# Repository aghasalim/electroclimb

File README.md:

<h1 align="center">ElectroClimb</h1>

<p align="center"><strong>An open-source legged robot that climbs concrete, glass and wood on electroadhesive feet,<br>controlled by reinforcement learning, and inspects structures as it goes.</strong></p>

<p align="center">
  <a href="docs/HOW_IT_WORKS.md">How it works</a> ·
  <a href="#the-model">The model</a> ·
  <a href="#ai-in-electroclimb">AI</a> ·
  <a href="docs/WALLSCAN.md">WallScan</a> ·
  <a href="hardware/foot/BUILD.md">Build a foot</a> ·
  <a href="sim/README.md">Simulation</a> ·
  <a href="inspection/README.md">Inspection</a> ·
  <a href="#roadmap">Roadmap</a>
</p>

> **Status:** everything here runs in simulation. **New (25 Nov 2026):** the robot now steers in any direction, goes from a wall onto a ceiling through a corner and trots under a ceiling on two pads, all with pads that only grip when flat. The same check showed the earlier results were too kind (pads gripped on their edges; the 88 % on hard walls becomes 42 %, or 82 % with a faster gait clock) and that the ankle must be much softer (the foot and hip CAD are changed to match, not yet printed): [`sim/README.md`](sim/README.md#flat-pads-steering-the-corner-and-the-ceiling-trot). The simulated robot climbs a vertical wall; the foot hardware (stage 1) is in progress. See [`hardware/foot/`](hardware/foot/) and [`sim/`](sim/).

<p align="center"><em>MuJoCo simulation, vertical wall and a 40 cm concrete pillar, 2× speed: baseline crawl gait with electroadhesive feet, 18 cm in 20 s without falling. Real physics, not an animation.</em></p>

<details>
<summary>Contents</summary>

- [The model](#the-model)
- [Repository](#repository)
- [Why](#why)
- [What makes it new](#what-makes-it-new)
- [How it works](#how-it-works)
- [AI in ElectroClimb](#ai-in-electroclimb)
- [New idea: WallScan, feet that see inside the wall](#new-idea-wallscan-feet-that-see-inside-the-wall)
- [The robot](#the-robot)
- [The learning](#the-learning)
- [Roadmap](#roadmap)
- [Hard problems](#hard-problems)
- [Who it's for](#who-its-for)
- [License](#license)
- [Author](#author)
- [Related work](#related-work)

</details>

## The model

| Part | What's modelled |
|---|---|
| **Motors** | 12 STS3215 servos (45.2 × 24.7 × 35 mm) in their mounting positions: 4 abduction servos in the chassis corners, 4 hip servos bolted to their horns, 4 knee servos built into the shins. Horns, case screws, mounting ears and cable exits included. |
| **Legs** | One outboard thigh plate per leg between the hip horn and the knee horn, a carbon shin tube, a ball ankle and the red high-voltage cable down each shin. |
| **Feet** | Flex-PCB pad with the two interdigitated copper combs, a TPU spider, and the HV driver board (HV module, reed relay, resistors, LED). Pads and LEDs glow while energised. |
| **Brain** | Electronics bay under a clear lid: brain PCB (CPU with heat sink and fan, RAM, flash, 4 CAN transceivers, IMU, GPIO header, leg connectors) and a power board. |
| **Enclosure** | Graphite chassis tub with cooling fins and grab rails, white bay rim, stereo camera nose with an inspection light, tail block with tether ring, antenna, e-stop and charge port, battery strapped under the belly. |

The whole model is generated by [`sim/make_assets.py`](sim/make_assets.py) (70 meshes, 36,000 triangles, 4 textures). It is visual only: the detailed parts have no mass and no contacts, so mass (1.46 kg), inertia and every simulation result are unchanged. It shows the intended layout; it is not a CAD model for manufacturing. The first real CAD is the foot: [`hardware/foot/cad/`](hardware/foot/cad/).

## Repository

| Path | What's there |
|---|---|
| [`hardware/foot/`](hardware/foot/) | Stage 1 foot: design spec, pad footprints (KiCad), BOM, **real CAD (STEP/STL)** and a [build guide](hardware/foot/BUILD.md) |
| [`hardware/`](hardware/README.md) | **Whole-robot hardware design** (not built): system scheme, wiring diagram, [bill of materials](hardware/BOM.md), the [driver board](hardware/foot/driver/) as a rule-checked KiCad PCB with Gerbers, and [body and leg CAD](hardware/robot/cad/) |
| [`tools/gen_electrode.py`](tools/gen_electrode.py) | Parametric electrode pad generator (`--selftest` checks for shorts) |
| [`tools/driver_calc.py`](tools/driver_calc.py) | HV driver component values + design-rule checks |
| [`sim/`](sim/) | MuJoCo model, climbing environment, crawl gait, physics checks, media renderer (stage 2) |
| [`inspection/`](inspection/) | Crack-detection CNN, RAG inspection assistant, LLM mission planner (stage 5) |
| [`sensing/`](sensing/) | WallScan: field solver and network for sensing inside the wall with the pad electrodes (simulation study) |
| [`media/`](media/) | Simulation GIFs and images (rendered by `sim/render_media.py`) |
| [`docs/HOW_IT_WORKS.md`](docs/HOW_IT_WORKS.md) | How it works: leg mechanism, gait, electroadhesion physics, peel moment, balance on three legs, HV driver, RL loop, results |
| [`docs/DESIGN.md`](docs/DESIGN.md), [`docs/LAUNCH_POSTS.md`](docs/LAUNCH_POSTS.md) | Visual language of the banner and images; draft launch posts |
| [`docs/`](docs/) | Sponsorship sheet |

## Why

Every bridge, dam, tower and facade needs regular inspection. Today that means scaffolding, rope access or drones that can't touch the surface. A robot that walks up the wall itself can get close enough to measure a crack, tap the concrete and come back down.

Climbing robots with learned controllers already exist, but they cling to **steel** with magnets. Most of the built world is concrete, glass, brick and wood, where magnets don't work.

**Electroadhesion** works on almost any surface. A thin pad with interdigitated electrodes at 1–3 kV (microamp current) induces charge in the surface and sticks to it, then releases instantly when switched off. The hard part is that adhesion depends on the surface, dust, humidity and how flat the contact is, and one bad step means a fall.

ElectroClimb treats that as a learning problem. Each foot senses its own grip through electrode capacitance, and a reinforcement learning policy decides where to step, how hard to press, when to energise each foot and when to peel it off.

## What makes it new

| | Existing learned climbers | ElectroClimb |
|---|---|---|
| Adhesion | Magnets (steel only) | Electroadhesion (concrete, glass, wood, painted walls) |
| Grip sensing | Assumed or estimated | Measured per foot (electrode capacitance) |
| Control | RL for walking, fixed adhesion | RL controls walking **and** adhesion (voltage, timing, peel) |
| Openness | Closed, research hardware | Fully open hardware, firmware, simulation, policies |
| Cost target | Lab robots | Under €2,000 in parts |

## How it works

<p align="center"><em>One leg stepping: the pad lets go, the foot lifts 2.5 cm, moves 4 cm up and sticks again.</em></p>

```mermaid
mindmap
  root((ElectroClimb))
    Legs
      3 servos per leg, 12 in total
      Thigh 8.1 cm, shin 6.7 cm
      Spring ankles keep pads flat
    Electroadhesion
      Comb electrodes at 1 to 3 kV
      Friction carries the weight
      Split pads survive drop-outs
    Sensing
      Pad capacitance shows contact
      IMU and servo positions
    Control
      Crawl gait, one leg at a time
      Never lift until 3 feet stick
      RL corrects the gait
```

- **Legs:** each leg has hip abduction, hip flexion and knee servos (Feetech STS3215). Inverse kinematics turns planned foot positions into joint angles. On a vertical wall the gait needs at most 0.9 N·m per joint.
- **Gait:** one foot moves at a time (release, lift, swing 4 cm, place until contact, stick), then the body pulls itself up on all four pads. A foot is only released when the other three report contact.
- **Physics:** the pads press the robot against the wall and friction carries the weight: 0.6 × pads × 15 N × grip must beat 14.3 N. With three pads that needs at least 53 % grip. The weight 9 cm from the wall also tries to peel the upper feet off (about 6.4 N), which is why the body crouches low.
- **Electronics:** each pad half has its own high-voltage driver board (XP Power A30P-5, 0–3 kV, microamp-limited), with a 1 GΩ safety bleeder and a reed relay that releases the pad in about 1 ms. The board is designed and rule-checked, not built: [`hardware/foot/driver/`](hardware/foot/driver/).

### How the feet stick

On a floor the robot needs no adhesion: gravity holds it down. On walls and ceilings it uses electroadhesion.

1. **The pad is a flexible circuit board.** Under a thin insulating layer it has two comb-shaped electrodes that interleave like fingers of two hands.
2. **A high voltage goes across the two combs:** 1 to 3 kV, one comb positive and one negative. The current is only microamps, so a pad uses well under a watt.
3. **The surface responds.** The electric field shifts charges inside the wall material under the pad. Opposite charges attract, so the pad is pulled onto the wall.
4. **On a wall, friction carries the weight.** The pull presses the pad against the surface and friction stops it sliding down. Under a ceiling the pull itself carries the weight.
5. **Switching off releases the foot.** A relay discharges the pad in about 1 ms, so the leg can lift and step.

It needs no air-tight seal like suction and no steel like magnets, so it works on glass, wood and painted concrete.

Two limits:

- **The pad must lie flat.** The pull only acts across a gap of micrometres. A pad tilted more than a few degrees does not grip, which is why each foot has a soft ankle ([`sim/README.md`](sim/README.md)).
- **The force is not measured yet.** The simulation assumes 15 N per pad. Rough, dusty or damp surfaces give less, and the first bench test of a real pad will give the true number.

**Standing on three legs.** Every step leaves three pads holding the robot. On a vertical wall that needs 55–58 % grip instead of 41 % on four pads, and lifting an upper leg is the worst case. A force model and MuJoCo agree on these numbers ([`sim/balance.py`](sim/balance.py)).

**Full explanation with diagrams: [docs/HOW_IT_WORKS.md](docs/HOW_IT_WORKS.md).**

### Latest simulation results

Success = no fall and at least 10 cm climbed in 20 s on 40 hard vertical test walls.

| | Success | Falls |
|---|---|---|
| Crawl gait, one-piece pads | 80 % | 15 % |
| Best RL policy, one-piece pads | 82 % | 12 % |
| **Crawl gait, split pads** | **88 %** | **12 %** |
| RL policy, split pads | 88 % | 12 % |
| Crawl gait, split pads, +10 % pad force | **95 %** | **2 %** |

Splitting each pad into two independently driven halves fixes random pad drop-outs. The rest is a margin question: about 10 % more pad force (bigger pads or a lighter robot) takes the plain gait to 95 %. Details in [`sim/README.md`](sim/README.md).

## AI in ElectroClimb

| Part | Method | Result | Code |
|---|---|---|---|
| Climbing control | Residual RL on a crawl gait: PPO, SAC, curriculum, teacher-student distillation (DAgger) | 88 % on 40 hard walls; 95 % with 10 % more pad force | [`sim/`](sim/README.md) |
| Crack detection | CNN on 40,000 concrete photos, tile scan of wall images | 99.25 % on 4,000 unseen photos | [`inspection/crack_model.py`](inspection/crack_model.py) |
| Inspection assistant | RAG: BM25 over the FHWA Bridge Inspector's Reference Manual + Claude with page citations | answers and defect reports cite manual pages | [`inspection/rag.py`](inspection/rag.py) |
| Subsurface sensing (WallScan) | Finite-difference field model + neural inverse on 36 electrode-pair capacitances | 91 % defect identification in simulation; untested on hardware | [`sensing/wallscan.py`](sensing/wallscan.py) |
| Mission planning | LLM (Claude) turns a sentence into a checked waypoint plan the robot climbs in simulation | holds within 0.03 cm at each inspection stop | [`inspection/mission.py`](inspection/mission.py) |
| Talking to the robot | Spoken orders and questions while it climbs: rules offline, Claude for free sentences; answers out loud | inspect, stop, resume, grip check, come down and report in one run | [`inspection/voice.py`](inspection/voice.py) |

Details: [`inspection/README.md`](inspection/README.md) and [`sim/README.md`](sim/README.md).

## New idea: WallScan, feet that see inside the wall

The pads that hold the robot could also scan the wall. With each pad's comb split into 8 separately wired strips, the 36 strip-pair capacitances carry information about what is under the foot. In a first simulation study, a neural network identifies voids, wet zones and rebar correctly in **91 %** of unseen footsteps and locates them within 2.4 mm sideways and 1.1 mm in depth; one capacitance per pad (today's grip sensing) manages 32 %. In a literature search, no published climbing robot was found that uses its adhesion electrodes to image the wall. This is simulation only, not yet measured on hardware. Details, sources and limits: [`docs/WALLSCAN.md`](docs/WALLSCAN.md).

## The robot

- **Body:** quadruped, about 40 cm and under 1.5 kg, with a 3D-printed carbon-fibre-nylon frame.
- **Legs:** 3 actuated joints per leg (12 total), using low-cost smart servos at first and custom quasi-direct-drive actuators in v2.
- **Feet:** flexible-PCB electroadhesive pads (polyimide doubles as the insulator) on compliant TPU backings, with a passive ankle so each pad can lie flat.
- **Foot electronics:** a small high-voltage driver per pad half (two per foot, so one fault only loses half a pad), current-limited, and a capacitance-sensing front end on the same electrodes for grip and contact sensing.
- **Compute:** Seeed XIAO microcontrollers per leg on a CAN bus, and a Raspberry Pi 5 or Jetson Orin Nano running the policy and vision.
- **Sensing:** IMU, joint encoders and currents, per-foot capacitance, front stereo camera.
- **Safety:** tether line during development, fall detection, and a hardware interlock so the high voltage is only on when the foot is in contact.

## The learning

1. **Adhesion model:** measure holding force against voltage, surface, dust, humidity and peel angle on a test rig. Fit a stochastic adhesion model to that data.
2. **Simulation:** model the robot in MuJoCo / Isaac Lab with the learned adhesion model, including random attachment failures, surface patches and dust.
3. **Curriculum RL:** train on thousands of parallel simulated environments while slowly tilting gravity from floor to vertical wall to overhang. Domain randomisation covers adhesion, friction, motor strength, latency and sensor noise.
4. **Teacher-student:** a teacher policy that sees true adhesion trains a student policy that only sees what the real robot senses (capacitance, IMU, joints).
5. **Sim-to-real:** deploy on the robot, tethered, first on a tilting test wall, then vertical, then real structures.
6. **Inspection:** an onboard vision model detects cracks and spalling, and the robot builds a 3D map of the wall with defects marked.

## Roadmap

| Stage | Goal | Done when |
|---|---|---|
| **1. Electroadhesive foot** (months 1–3) | Pad design, high-voltage driver, capacitance sensing, adhesion test rig | Reliable hold on concrete, glass and wood, and grip measured from capacitance |
| **2. Adhesion model + simulation** (months 2–5) | Data-driven adhesion model, robot simulation, first trained climbing policy in sim | A policy climbs a vertical wall in simulation and survives random adhesion failures |
| **3. Robot v1** (months 4–7) | Build the quadruped and electronics, and get it walking on the floor | Walks with an RL policy transferred from simulation |
| **4. Real climbing** (months 6–10) | Tilt-wall curriculum on hardware, then vertical | Climbs 2 m of vertical concrete and glass on a tether, without falling |
| **5. Inspection** (months 9–12) | Crack-detection model, mapping, floor-to-wall transitions | Climbs a real wall and returns a map of defects |
| **6. Release** (month 12) | Build guide, datasets, trained policies, paper | Everything open, and a paper submitted (ICRA / IROS / RA-L) |

## Hard problems

- **Adhesion you can't fully see:** grip changes with dust, moisture and micro-texture, so the policy must act on noisy, partial information.
- **Contact dynamics in simulation:** electrostatic adhesion is not built into physics engines, so it has to be modelled and learned from data.
- **High voltage on a moving robot:** insulation, creepage, current limiting and interlocks have to survive vibration and falls.
- **Power and weight:** every gram counts on a vertical wall, while the robot carries compute, batteries and four high-voltage drivers.
- **Transitions:** going from floor to wall and wall to ledge are the hardest manoeuvres in climbing.

## Who it's for

- **Infrastructure owners and inspectors:** close-up inspection without scaffolding.
- **Researchers:** an open platform and benchmark for learned adhesion and climbing.
- **Students:** a full robotics stack covering hardware, embedded, simulation, RL, vision and safety.

## License

Software, firmware and models: MIT, see [`LICENSE`](LICENSE).
Hardware design files in `hardware/`: CERN-OHL-S v2, see [`hardware/LICENSE`](hardware/LICENSE).

## Author

Aghasalim Mustafazada, Creative Technologies & AI, Howest University of Applied Sciences (Belgium)
Previous project: [smart-ivc-cage-platform](https://github.com/aghasalim/smart-ivc-cage-platform)

## Related work

- Um et al., *Reinforcement Learning-based Robust Wall Climbing Locomotion Controller in Ferromagnetic Environment*, arXiv:2510.20174 (2025). Magnetic feet on steel.
- *Magnecko: Design and Control of a Quadrupedal Magnetic Climbing Robot*, arXiv:2504.13672 (2025).
- Hemsing, *electrostatic-adhesion-plate*, open-source electroadhesion PCB (CERN-OHL-S).

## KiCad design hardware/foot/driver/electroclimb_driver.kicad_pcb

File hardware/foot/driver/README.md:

# Foot driver board v1

> ⚠️ **High voltage.** This board makes up to 3 kV. The current is limited to microamps, but it can still give a painful shock and destroy electronics. Build and power it only with a supervisor.

> **Status: designed and rule-checked by script, never manufactured, never powered.** KiCad's design-rule check reports 0 errors and 0 unconnected pads. That proves the copper matches the netlist and keeps its distances. It does not prove the circuit works. Read [Open points](#open-points-before-ordering) before ordering.

One board drives one electroadhesive pad: it sets the pad voltage (0–3 kV), limits the current, releases the pad in about a millisecond, and measures pad voltage and charge so the robot knows how well the foot grips.

Schematic: [`../driver_schematic.svg`](../driver_schematic.svg)

## Files

| File | What it is |
|---|---|
| [`driver_board.py`](driver_board.py) | **The source.** Parts, pin-to-net table, placement, the hand-routed high-voltage tracks and a small router for the rest. Change it and run `build.sh`. |
| [`electroclimb_driver.kicad_pcb`](electroclimb_driver.kicad_pcb) | The board, opens in KiCad 10. 82 × 50 mm, 2 layers. |
| [`electroclimb_driver.kicad_dru`](electroclimb_driver.kicad_dru) | The high-voltage spacing rule KiCad checks: 5.5 mm from any high-voltage copper to anything else. |
| [`fab/electroclimb_driver.zip`](fab/electroclimb_driver.zip) | Gerber and drill files, plus the placement file for assembly. |
| [`bom.csv`](bom.csv) | Parts list for one board, with the part to order. |
| [`netlist.md`](netlist.md) | Every net and the pins on it. |
| [`drc.rpt`](drc.rpt) | KiCad's check report for the committed board. |
| [`build.sh`](build.sh) | Regenerates everything above and fails if KiCad finds an error. |

```bash
./build.sh
```

## How it works

| Block | Parts | What it does |
|---|---|---|
| High-voltage module | U1 XP Power A30P-5 | 5 V in, 0–3 kV out, 1 W. Its control pin sets the output from 0 to 100 %. |
| Voltage setpoint | R1, C1, R11, U3, R8–R10, C5 | The XIAO's PWM (3.3 V) is filtered and multiplied by 1.51, because the control pin needs 0–5 V. With no PWM, R11 holds the setpoint at 0 V. |
| Current limit | R2 47 MΩ | A shorted pad draws 64 µA at most. |
| Bleeder and voltage monitor | R3 1 GΩ, R7 750 kΩ, R12, C6, D2 | Always connected: empties the pad in seconds if everything else fails. The same divider reports the real pad voltage (2.15 V at full voltage), so firmware can regulate it. The module itself is not regulated and overshoots at light load. |
| Fast release | K1, R4 1 MΩ, Q1, D4, R13, R14 | The reed relay shorts the pad through 1 MΩ: empty in about 1 ms. |
| Grip sensing | R5 10 kΩ, R6, D1 | The pad's charging current returns through R5 at ground level. Its integral is the charge; charge divided by voltage is the capacitance, which rises when the pad touches a surface. |
| Interlock | J2, R16, R17 | The module's 5 V feed arrives on its own wire, already switched by the arm key and the E-stop on the body, and passes through the foot contact switch on J2. No software is involved. The XIAO only reads whether it is armed. |
| CAN | U4, R18, R19, JP1 | 500 kbit/s to the Raspberry Pi. Fit the JP1 jumper on the last board of the bus. |

XIAO pins: D3 PWM, D0 pad current, D1 pad voltage, D8 release relay, D9 armed, D10 LED, D4 CAN TX, D5 CAN RX. Firmware is not written yet.

Values are checked by [`tools/driver_calc.py`](../../../tools/driver_calc.py). Run it after changing any resistor.

## Layout choices

- **High voltage on the right, logic on the left.** The three high-voltage nets (`HV_OUT`, `PAD_A`, `DUMP`) are routed by hand on the bottom layer.
- **5.5 mm spacing** from high-voltage copper to everything else. The relay sets this number: its coil pins are 7.62 mm from its contact pins. General-purpose spacing tables ask for more at 3 kV (roughly 8 mm with coating), so **coat the high-voltage area** with conformal coating or silicone after soldering and testing.
- **No top-side tracks under the module or under the high-voltage resistors.** XP Power asks for this under the module; the resistor bodies sit at up to 3 kV.
- **Nylon M3 screws and spacers** in the three mounting holes.
- The XIAO goes on two 1 × 7 pin sockets with its USB-C plug towards the board edge (marked `USB`).
- Footprints for U1, K1, R2, R3 and R4 were drawn from the manufacturers' drawings (XP Power A series p. 6, Standex-Meder SHV p. 3, Vishay VR25/VR37/VR68, Ohmite Mini-Mox).

## Open points before ordering

1. **Relay switching rating.** K1 (Standex-Meder SHV05-1A85, 4 kV version) may stand off 4 kV but is rated to *switch* 1 kV. Here it closes onto up to 3 kV, through 1 MΩ: 3 mA peak and 4.5 mJ. That is a small load, but it is outside the datasheet. Either test it on the bench for contact life, or fit a relay rated to switch the full voltage. The ones found are much larger: Cynergy3 DAT70510 (60 mm long, 23 g) or Standex-Meder HE12-1A83 (12 V coil). No small 5 V relay rated to switch above 3 kV was found.
2. **Relay coil polarity.** The SHV order code has an option letter (`D` or `L`) whose meaning the series datasheet does not explain. If `D` is an internal diode, the coil has a polarity: check the product datasheet. The board puts +5 V on pin 2.
3. **BAV199 pin numbers.** The clamp diodes D1 and D2 assume pin 1 = anode, pin 2 = cathode, pin 3 = common. The datasheet read for this design did not print pin numbers.
4. **Print the board 1:1 on paper** and lay U1, K1 and the high-voltage resistors on it before ordering. No footprint has been test-fitted.
5. **Sponsor logo.** The silkscreen has an empty box marked `LOGO`. AISLER's sponsorship asks for their logo on the silkscreen from the first order: place their artwork there in KiCad before uploading.
6. **One board per pad.** The simulation's best results use pads split into two halves. That needs two of these boards per foot, or a two-channel version of this board.
7. **Cost.** The A30P-5 costs about €270 (DigiKey, November 2026). No module under €100 with these ratings was found.
8. **Spacing review.** Ask the lab supervisor to review the high-voltage spacing and the coating before the first power-up.

## Ordering

Upload `electroclimb_driver.kicad_pcb` (AISLER takes KiCad files directly) or `fab/electroclimb_driver.zip`. 2 layers, 1.6 mm FR4, any solder mask colour. A stencil helps for the 0805 parts.

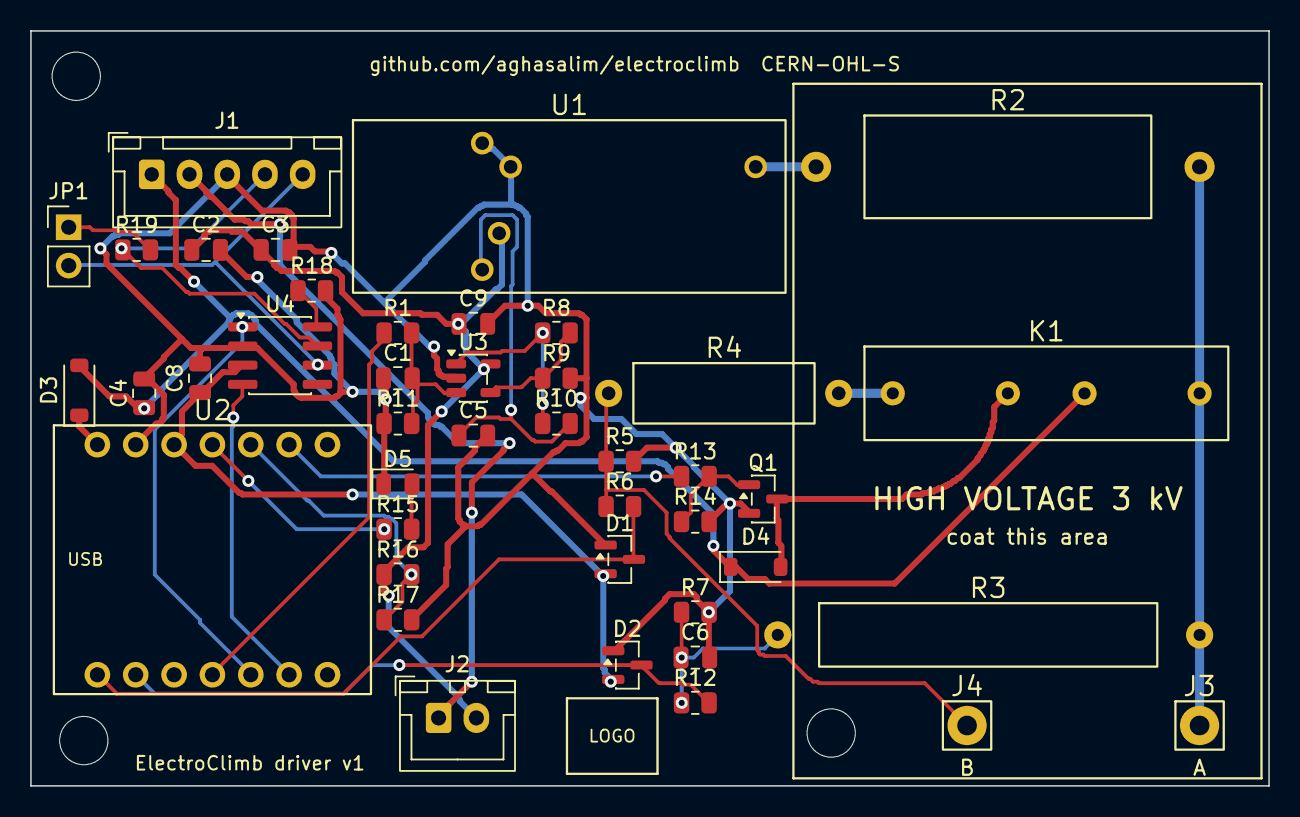
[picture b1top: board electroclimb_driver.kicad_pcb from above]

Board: 2 copper layers, 82.0 x 50.0 mm, 43 parts (0 on the bottom side), 30 nets.

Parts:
C1: 1u; C_0805_2012Metric
C2, C4: 10u; C_0805_2012Metric
C3, C5, C8, C9: 100n; C_0805_2012Metric
C6: 1n; C_0805_2012Metric
D1, D2: BAV199; SOT-23
D3: schottky; D_SOD-123
D4: 1N4148W; D_SOD-123
D5: red; LED_0805_2012Metric
J1: leg cable; JST_XH_B5B-XH-A_1x05_P2.50mm_Vertical
J2: contact switch; JST_XH_B2B-XH-A_1x02_P2.50mm_Vertical
J3: PAD A
J4: PAD B
JP1: CAN end; PinHeader_1x02_P2.54mm_Vertical
K1: SHV05-1A85-78x4K
Q1: 2N7002; SOT-23
R1, R5, R9, R16, R18: 10k; R_0805_2012Metric
R2: 47M
R3: 1G
R4: 1M
R6, R10, R12, R15: 1k; R_0805_2012Metric
R7: 750k; R_0805_2012Metric
R8: 5k1; R_0805_2012Metric
R11, R14: 100k; R_0805_2012Metric
R13: 100R; R_0805_2012Metric
R17: 15k; R_0805_2012Metric
R19: 120R; R_0805_2012Metric
U1: A30P-5
U2: XIAO ESP32-S3
U3: MCP6001; SOT-23-5
U4: SN65HVD230; SOIC-8_3.9x4.9mm_P1.27mm

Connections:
3V3: C8.1, D1.2, D2.2, U2.3V3, U4.3
5V_XIAO: D3.1, U2.5V
+5V: C4.1, D3.2, D4.1, J1.1, K1.2
+5V_ARM: J1.2, J2.1
ARM_S: R16.2, R17.1, U2.D9
CANH: J1.4, R19.1, U4.7
CANL: J1.5, JP1.2, U4.6
CAN_RX: U2.D5, U4.4
CAN_TX: U2.D4, U4.1
COIL_N: D4.2, K1.3, Q1.3
CTRL: C5.1, R10.2, U1.5
CTRL_O: R8.1, R10.1, U3.1
DUMP: K1.4, R4.1
FB: R8.2, R9.1, U3.4
GATE: Q1.1, R13.2, R14.1
GND: C1.1, C2.2, C3.2, C4.2, C5.2, C6.2, C8.2, C9.2, D1.1, D2.1, D5.1, J1.3, Q1.2, R5.2, R7.2, R9.2, R11.1, R14.2, R17.2, R18.2, U1.1, U1.4, U2.GND, U3.2, U4.2
HV_OUT: R2.1, U1.3
ISENSE: D1.3, R6.2, U2.D0
LED: R15.1, U2.D10
LED_A: D5.2, R15.2
PAD_A: J3.1, K1.1, R2.2, R3.1
PAD_B: J4.1, R4.2, R5.1, R6.1
PWM: R1.1, U2.D3
RELAY: R13.1, U2.D8
RS: R18.1, U4.8
SET_F: C1.2, R1.2, R11.2, U3.3
TERM: JP1.1, R19.2
VHV_IN: C2.1, C3.1, C9.1, J2.2, R16.1, U1.2, U3.5
VMON: C6.1, R3.2, R7.1, R12.1
VMON_ADC: D2.3, R12.2, U2.D1

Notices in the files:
README.md:
Software licence: MIT
Hardware licence: CERN-OHL-S v2
hardware/foot/driver/electroclimb_driver.kicad_pcb:
github.com/aghasalim/electroclimb  CERN-OHL-S
